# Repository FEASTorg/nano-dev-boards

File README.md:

# nano-dev-boards

Nano-format MCU development boards designed in KiCad.

## Status

The development status of various versions of the Arduino Nano V3.3 KiCAD project is indicated below:

| Project       | Status                                                                                                      | Description                                                 |
| ------------- | ----------------------------------------------------------------------------------------------------------- | ----------------------------------------------------------- |
| Nano Every    |  | Nano format featuring ATmega4809 microcontroller.           |
| Nano Original |          | A recreation of the beloved Arduino Nano V3.3.              |
| Nano Shield   |          | A breakout shield board for Nano-format development boards. |

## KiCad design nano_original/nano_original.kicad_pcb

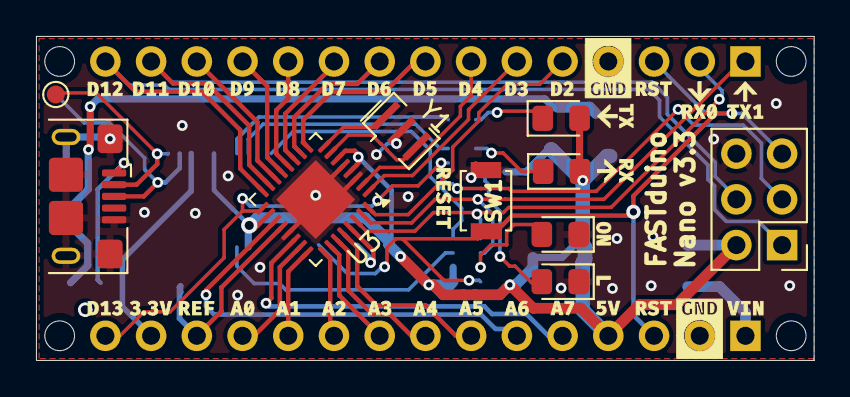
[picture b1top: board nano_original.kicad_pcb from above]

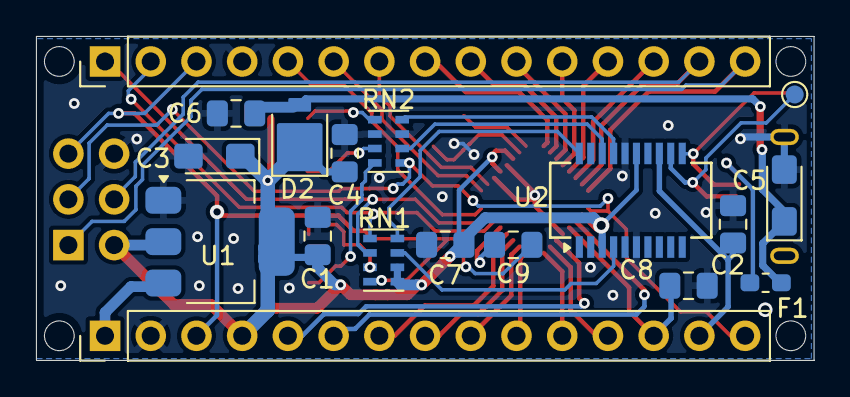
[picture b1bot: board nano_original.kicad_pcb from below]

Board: 2 copper layers, 43.2 x 18.0 mm, 29 parts (18 on the bottom side), 43 nets.

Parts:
C1, C4, C7: 1u; C_0805_2012Metric_Pad1.18x1.45mm_HandSolder
C2, C6, C8, C9: 100n; C_0805_2012Metric_Pad1.18x1.45mm_HandSolder
C3, C5: 4.7u; CP_EIA-3216-18_Kemet-A_HandSolder
D1: LED_Green_POW; LED_0805_2012Metric_Pad1.15x1.40mm_HandSolder
D2: SS1P3L; D_SMP_DO-220AA
D3: LED_Red_RX; LED_0805_2012Metric_Pad1.15x1.40mm_HandSolder
D4: LED_Green_TX; LED_0805_2012Metric_Pad1.15x1.40mm_HandSolder
D5: LED_Orange_ONB; LED_0805_2012Metric_Pad1.15x1.40mm_HandSolder
F1: PTC RESET FUSE; Fuse_0603_1608Metric_Pad1.05x0.95mm_HandSolder
J1: USB_B_Micro; USB_Micro-B_Amphenol_10118193-0001LF_Horizontal
J2, J3: Conn_01x15; PinHeader_1x15_P2.54mm_Vertical
J4: Conn_02x03_Odd_Even; PinHeader_2x03_P2.54mm_Vertical
RN1, RN2: 1k; R_Cat16-4
SW1: SW_Push; SW_SPST_B3U-1000P
Silkscreen_Front: Silkscreen_Back; Silkscreen_Front
TP1: D+; TestPoint_Pad_D1.0mm
TP2: D-; TestPoint_Pad_D1.0mm
U1: LM1117MP-5.0; SOT-223-3_TabPin2
U2: FT231XS; SSOP-20_3.9x8.7mm_P0.635mm
U3: ATmega328P-MUR; QFN-32-1EP_5x5mm_P0.5mm_EP3.1x3.1mm
Y1: 16MHz; Resonator_SMD_Murata_CSTxExxV-3Pin_3.0x1.1mm

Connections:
+3.3V: C2.1, J3.14, U2.13 (3V3OUT)
+5V: C1.1, C3.1, C4.1, C7.1, D2.1 (K), D3.2 (A), D4.2 (A), J3.4, J4.2, RN1.5 (R4.2), RN1.6 (R3.2), U1.2 (VO), U2.3 (VCCIO), U2.15 (VCC), U3.4 (VCC), U3.6 (VCC), U3.18 (AVCC)
/A0: J3.12, U3.23 (PC0)
/A1: J3.11, U3.24 (PC1)
/A2: J3.10, U3.25 (PC2)
/A3: J3.9, U3.26 (PC3)
/A4: J3.8, U3.27 (PC4)
/A5: J3.7, U3.28 (PC5)
/A6: J3.6, U3.19 (ADC6)
/A7: J3.5, U3.22 (ADC7)
/AREF: C8.1, J3.13, U3.20 (AREF)
/D0/RX: J2.2, RN1.1 (R1.1), U3.30 (PD0)
/D1/TX: J2.1, RN1.2 (R2.1), U3.31 (PD1)
/D2: J2.5, U3.32 (PD2)
/D3: J2.6, U3.1 (PD3)
/D4: J2.7, U3.2 (PD4)
/D5: J2.8, U3.9 (PD5)
/D6: J2.9, U3.10 (PD6)
/D7: J2.10, U3.11 (PD7)
/D8: J2.11, U3.12 (PB0)
/D9: J2.12, U3.13 (PB1)
/D10: J2.13, U3.14 (PB2)
/D11/MOSI: J2.14, J4.4, U3.15 (PB3)
/D12/MISO: J2.15, J4.1, U3.16 (PB4)
/D13/SCK: J3.15, J4.3, RN2.1 (R1.1), U3.17 (PB5)
/RESET: C9.2, J2.3, J3.3, J4.5, RN1.4 (R4.1), SW1.2
/RX: RN1.8 (R1.2), U2.20 (TXD)
/TX: RN1.7 (R2.2), U2.4 (RXD)
GND: C1.2, C2.2, C3.2, C4.2, C5.2, C6.2, C7.2, C8.2, D1.1 (K), D5.1 (K), J1.5 (GND), J1.6 (Shield), J2.4, J3.2, J4.6, RN2.3 (R3.1), RN2.6 (R3.2), SW1.1, U1.1 (GND), U2.6 (GND), U2.16 (GND), U3.3 (GND), U3.5 (GND), U3.21 (GND), U3.33 (GND), Y1.2
unnamed: D1.2 (A), RN1.3 (R3.1)
unnamed: D3.1 (K), RN2.7 (R2.2)
unnamed: D4.1 (K), RN2.5 (R4.2)
unnamed: D5.2 (A), RN2.8 (R1.2)
unnamed: J1.3 (D+), TP1.1, U2.12 (USBDM)
unnamed: J1.2 (D-), TP2.1, U2.11 (USBDP)
unnamed: F1.1, J1.1 (VBUS)
unnamed: RN2.2 (R2.1), U2.18 (CBUS0)
unnamed: RN2.4 (R4.1), U2.17 (CBUS1)
unnamed: U3.7 (XTAL1/PB6), Y1.3
unnamed: U3.8 (XTAL2/PB7), Y1.1
unnamed: C9.1, U3.29 (~RESET/PC6)
VIN: J3.1, U1.3 (VI)
VUSB: C5.1, C6.1, D2.2 (A), F1.2

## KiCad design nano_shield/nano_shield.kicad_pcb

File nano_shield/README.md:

# nano_shield

References:

- https://wiki.dfrobot.com/Arduino_Nano_IO_Shield__SKU__DFR0012_
- https://raw.githubusercontent.com/Arduinolibrary/DFRobot_Nano_shield/master/Nano%20Expansion%20V1.1.pdf

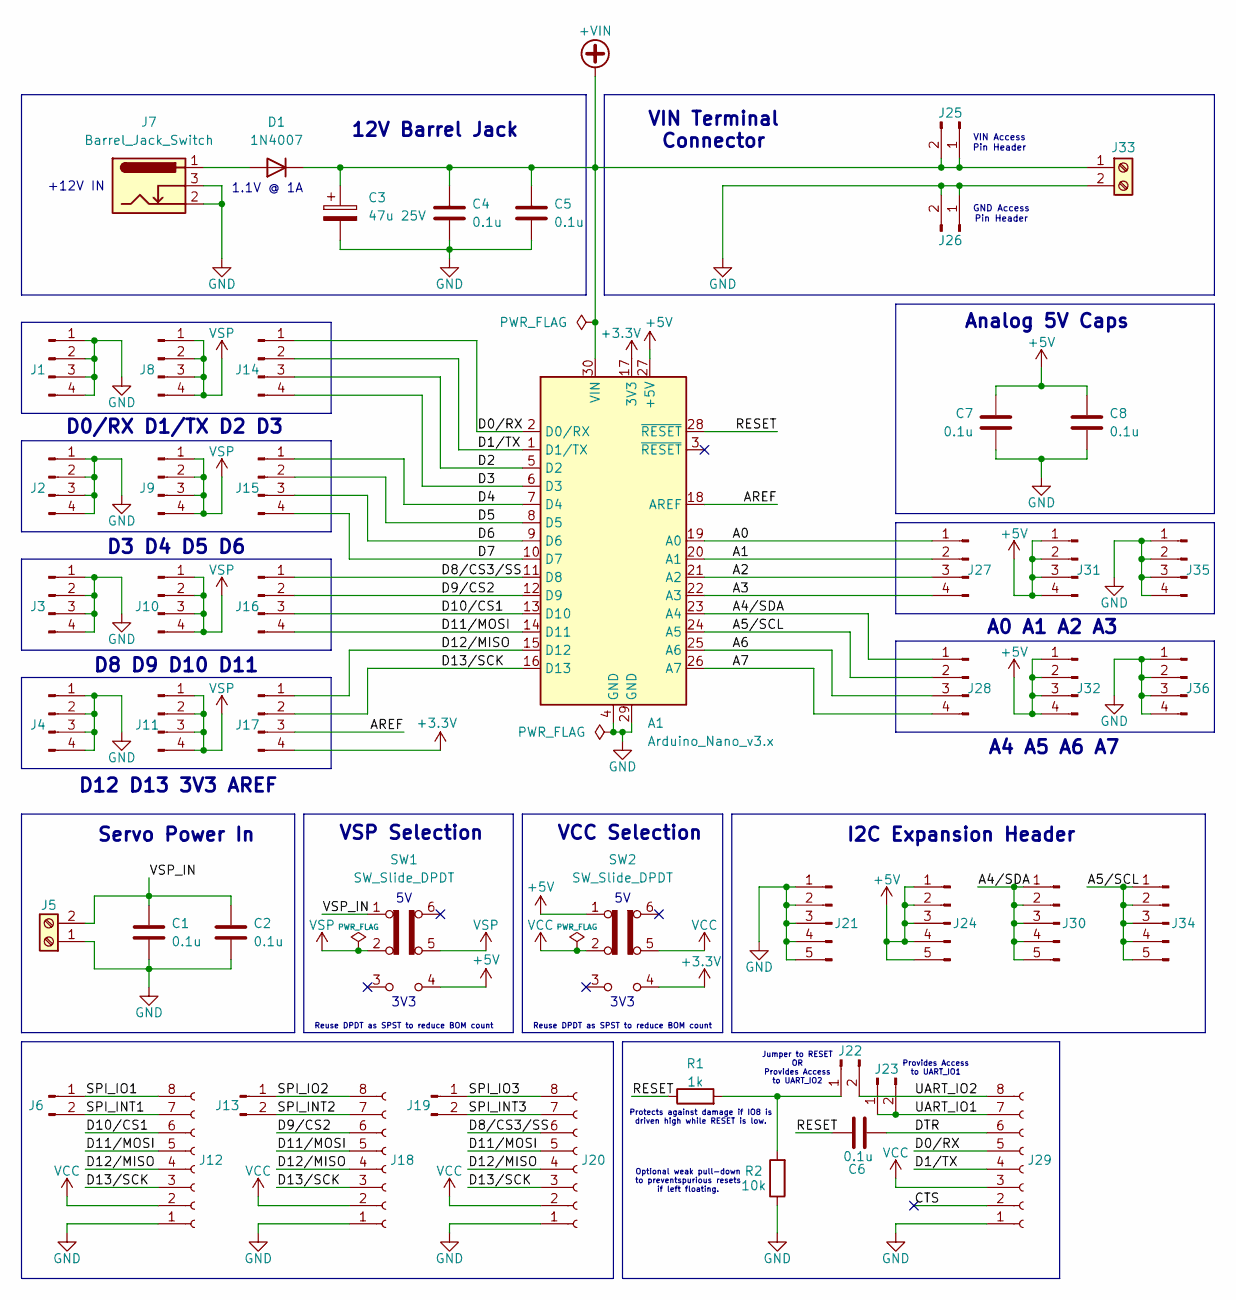
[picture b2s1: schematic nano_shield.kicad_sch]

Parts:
A1: Arduino_Nano_v3.x; Arduino_Nano
C1, C2, C4, C5, C6, C7, C8: 0.1u; C_0805_2012Metric_Pad1.18x1.45mm_HandSolder
C3: 47u 25V; CP_Elec_6.3x7.7
D1: 1N4007; D_SOD-123F
J1, J2, J3, J4, J8, J9, J10, J11, J14, J15, J16, J17, J27, J28, J31, J32, J35, J36: Conn_01x04_Pin; PinHeader_1x04_P2.54mm_Vertical_TightCY
J5, J33: Screw_Terminal_01x02; TerminalBlock_4Ucon_1x02_P3.50mm_Horizontal
J6, J13, J19, J22, J23, J25, J26: Conn_01x02_Pin; PinHeader_1x02_P2.54mm_Vertical_TightCY
J7: Barrel_Jack_Switch; BarrelJack_Horizontal
J12, J18, J20, J29: Conn_01x08_Socket; PinSocket_1x08_P2.54mm_Vertical_TightCY
J21, J24, J30, J34: Conn_01x05_Pin; PinHeader_1x05_P2.54mm_Vertical_TightCY
R1: 1k; R_0805_2012Metric_Pad1.20x1.40mm_HandSolder
R2: 10k; R_0805_2012Metric_Pad1.20x1.40mm_HandSolder
SW1, SW2: SW_Slide_DPDT; SW_DPDT_CK_JS202011JCQN

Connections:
+3.3V: A1.17 (3V3), J17.4, SW2.4 (A)
+5V: A1.27 (+5V), C7.1, C8.1, J24.1, J24.2, J24.3, J24.4, J24.5, J31.1, J31.2, J31.3, J31.4, J32.1, J32.2, J32.3, J32.4, SW1.4 (A), SW2.1 (A)
+VIN: A1.30 (VIN), C3.1, C4.1, C5.1, D1.1 (K), J25.1, J25.2, J33.1
/A0: A1.19 (A0), J27.1
/A1: A1.20 (A1), J27.2
/A2: A1.21 (A2), J27.3
/A3: A1.22 (A3), J27.4
/A4/SDA: A1.23 (A4), J28.1, J30.1, J30.2, J30.3, J30.4, J30.5
/A5/SCL: A1.24 (A5), J28.2, J34.1, J34.2, J34.3, J34.4, J34.5
/A6: A1.25 (A6), J28.3
/A7: A1.26 (A7), J28.4
/AREF: A1.18 (AREF), J17.3
/CTS: J29.2
/D0/RX: A1.2 (D0/RX), J14.1, J29.5
/D1/TX: A1.1 (D1/TX), J14.2, J29.4
/D2: A1.5 (D2), J14.3
/D3: A1.6 (D3), J14.4
/D4: A1.7 (D4), J15.1
/D5: A1.8 (D5), J15.2
/D6: A1.9 (D6), J15.3
/D7: A1.10 (D7), J15.4
/D8/CS3/SS: A1.11 (D8), J16.1, J20.6
/D9/CS2: A1.12 (D9), J16.2, J18.6
/D10/CS1: A1.13 (D10), J12.6, J16.3
/D11/MOSI: A1.14 (D11), J12.5, J16.4, J18.5, J20.5
/D12/MISO: A1.15 (D12), J12.4, J17.1, J18.4, J20.4
/D13/SCK: A1.16 (D13), J12.3, J17.2, J18.3, J20.3
/DTR: C6.2, J29.6
/RESET: A1.28 (~RESET), C6.1, R1.1
/SPI_INT1: J6.2, J12.7
/SPI_INT2: J13.2, J18.7
/SPI_INT3: J19.2, J20.7
/SPI_IO1: J6.1, J12.8
/SPI_IO2: J13.1, J18.8
/SPI_IO3: J19.1, J20.8
/UART_IO1: J23.1, J23.2, J29.7
/UART_IO2: J22.2, J29.8
/VSP_IN: C1.1, C2.1, J5.2, SW1.1 (A)
GND: A1.4 (GND), A1.29 (GND), C1.2, C2.2, C3.2, C4.2, C5.2, C7.2, C8.2, J1.1, J1.2, J1.3, J1.4, J2.1, J2.2, J2.3, J2.4, J3.1, J3.2, J3.3, J3.4, J4.1, J4.2, J4.3, J4.4, J5.1, J7.2, J7.3, J12.1, J18.1, J20.1, J21.1, J21.2, J21.3, J21.4, J21.5, J26.1, J26.2, J29.1, J33.2, J35.1, J35.2, J35.3, J35.4, J36.1, J36.2, J36.3, J36.4, R2.1
unnamed: D1.2 (A), J7.1
unnamed: J22.1, R1.2, R2.2
VCC: J12.2, J18.2, J20.2, J29.3, SW2.2 (B), SW2.5 (B)
VSP: J8.1, J8.2, J8.3, J8.4, J9.1, J9.2, J9.3, J9.4, J10.1, J10.2, J10.3, J10.4, J11.1, J11.2, J11.3, J11.4, SW1.2 (B), SW1.5 (B)

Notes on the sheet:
D0/RX D1/TX D2 D3
D8 D9 D10 D11
Analog 5V Caps
GND Access Pin Header
D3 D4 D5 D6
Jumper to RESET OR Provides Access to UART_IO2
1.1V @ 1A
+12V IN
VSP Selection
D12 D13 3V3 AREF
VIN Access Pin Header
3V3
Protects against damage if IO8 is driven high while RESET is low.
Reuse DPDT as SPST to reduce BOM count
A0 A1 A2 A3
Provides Access to UART_IO1
VCC Selection
A4 A5 A6 A7
Servo Power In
VIN Terminal Connector
Optional weak pull-down to preventspurious resets if left floating.
I2C Expansion Header
12V Barrel Jack

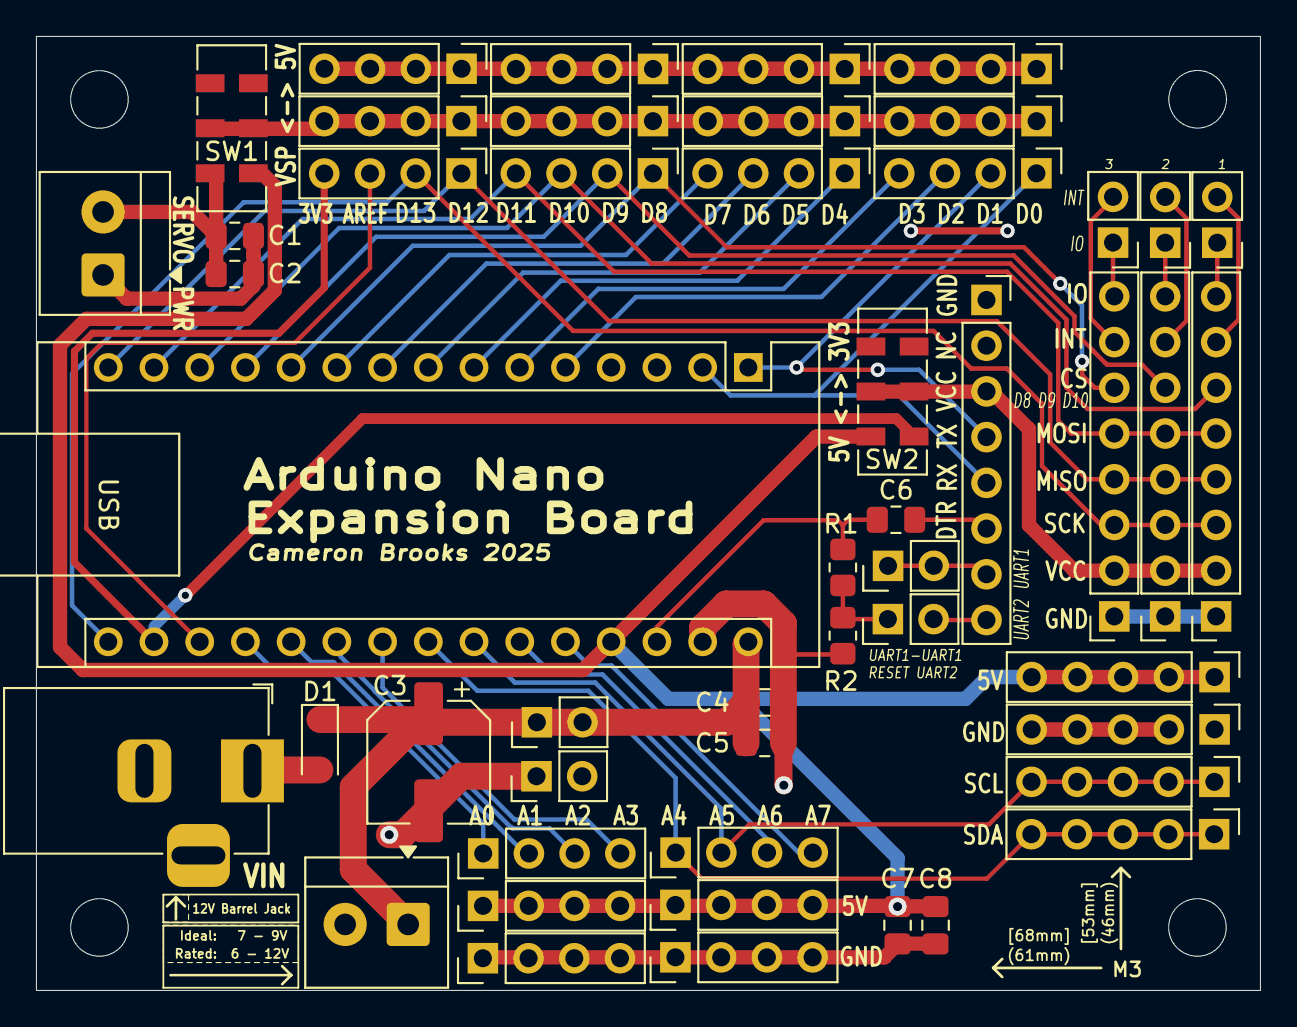
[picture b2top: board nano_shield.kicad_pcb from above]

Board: 2 copper layers, 68.0 x 53.0 mm, 50 parts (0 on the bottom side), 42 nets.

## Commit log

2025-04-21 added docs
2025-04-22 updated BOM
2025-11-25 tranfer: nano shield from other repo
2025-11-25 update docs for recent changes
2025-11-25 rename shield to use underscore
2025-11-25 untrack prl
2025-11-25 untrack fp-info-cache
2025-11-25 s to reademe title for nanoS
2025-11-25 rename to remove v3
2025-11-25 update procurement spreadsheets and clean backups
2025-11-25 update procurement for shield
2026-01-27 update name
2026-01-31 licensing: add cern hw license
2026-01-31 licensing: update front license
2026-01-31 change informative front license to md for viewing
2026-02-07 critical fix: swap tx and rx between atmega328p and ft231 (smooth brain moment)
